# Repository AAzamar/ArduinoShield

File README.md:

# ArduinoShield
Shield de programación, depurado y prototipado para ESP-01 con Arduino UNO.
Colocar las librerías en el mismo directorio que el proyecto para adquirir adecuadamente las huellas y modelos 3D.

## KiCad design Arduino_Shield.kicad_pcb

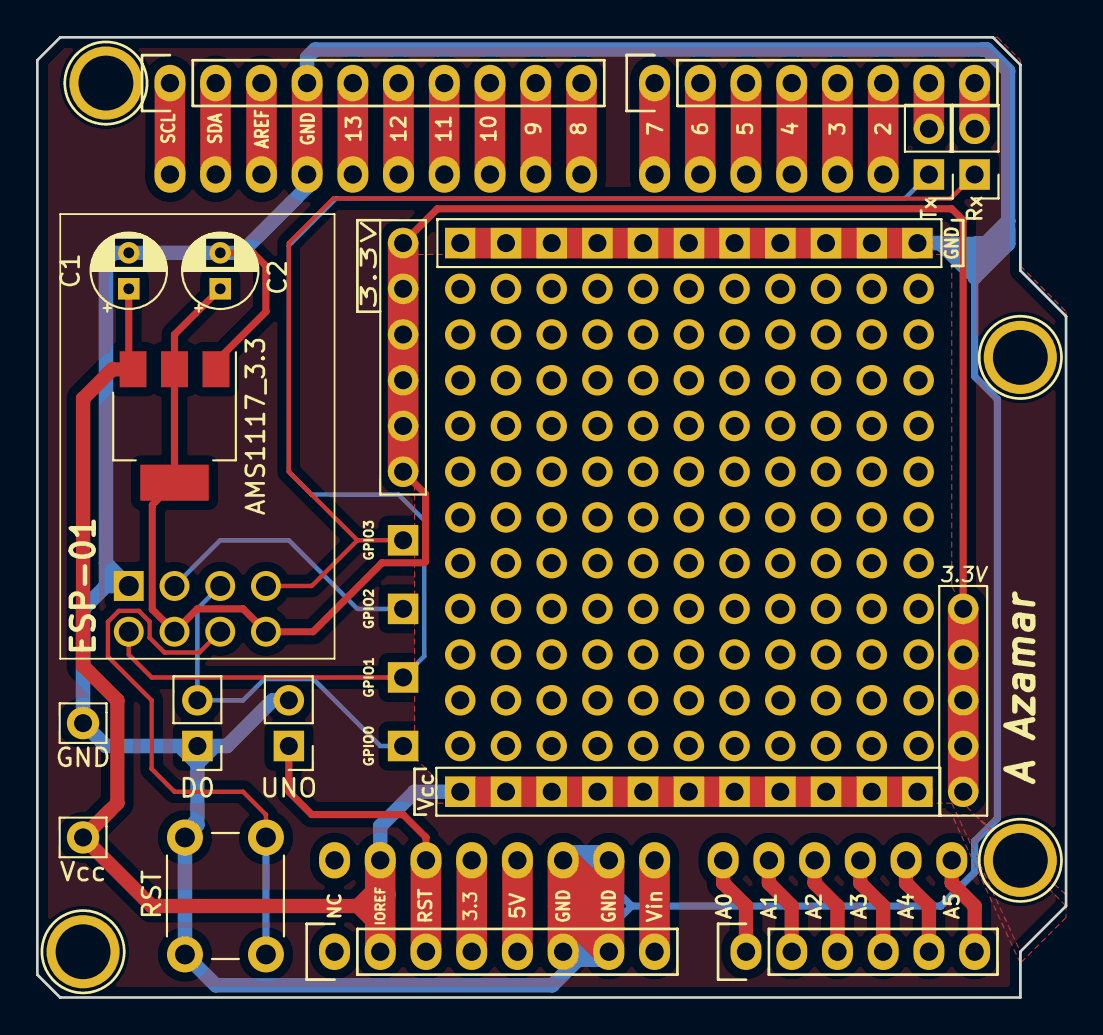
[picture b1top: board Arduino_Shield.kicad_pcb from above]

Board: 2 copper layers, 57.2 x 53.3 mm, 42 parts (0 on the bottom side), 35 nets.

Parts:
AMS1117_3.3: AMS1117-3.3; SOT-223-3_TabPin2
C1, C2: C; CP_Radial_D4.0mm_P2.00mm
D0: Conn_01x02_Male; PinHeader_1x02_P2.54mm_Vertical
ESP-01: ESP-01; ESP01
GND: MountingHole_Pad; Pin_D0.9mm_L10.0mm_W2.4mm_FlatFork
GND2: Conn_01x05; PinHeader_1x05_P2.54mm_Vertical
H2: GPIO0; PinHeader_1x01_P2.54mm_Vertical
H3: GPIO1; PinHeader_1x01_P2.54mm_Vertical
H4: GPIO2; PinHeader_1x01_P2.54mm_Vertical
H5: GPIO3; PinHeader_1x01_P2.54mm_Vertical
J1, J4: Conn_01x11; Pin_11_GND
J2, J3, J5, J6, J7, J8, J9, J10, J11, J12, J13: Conn_01x11; Pin11
P1, P9: Power; Socket_Strip_Arduino_1x08
P2, P10, P12: Analog; Socket_Strip_Arduino_1x06
P3, P11: Digital; Socket_Strip_Arduino_1x10
P4: Digital; Socket_Strip_Arduino_1x08
P5, P6, P7, P8: CONN_01X01; Arduino_1pin
P14: 3.3V; PinHeader_1x06_P2.54mm_Vertical
RST: SW_Push; SW_PUSH_6mm
Rx1: Conn_01x02_Male; PinHeader_1x02_P2.54mm_Vertical
Tx1: Conn_01x02_Male; PinHeader_1x02_P2.54mm_Vertical
UNO: Conn_01x02_Male; PinHeader_1x02_P2.54mm_Vertical
Vcc: MountingHole_Pad; Pin_D0.9mm_L10.0mm_W2.4mm_FlatFork

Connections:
+3V3: P1.4, P9.4
+5V: P1.5, P9.5
/0(Rx): P4.8, Rx1.2
/1(Tx): P4.7, Tx1.2
/2: P4.6, P12.6
/3(**): P4.5, P12.5
/3.3V: AMS1117_3.3.2, C2.1, ESP-01.6, ESP-01.8, GND2.1, GND2.2, GND2.3, GND2.4, GND2.5, P14.1, P14.2, P14.3, P14.4, P14.5, P14.6
/4: P4.4, P12.4
/5(**): P4.3, P12.3
/6(**): P4.2, P12.2
/7: P4.1, P12.1
/8: P3.10, P11.10
/9(**): P3.9, P11.9
/10(**/SS): P3.8, P11.8
/11(**/MOSI): P3.7, P11.7
/12(MISO): P3.6, P11.6
/13(SCK): P3.5, P11.5
/A0: P2.1, P10.1
/A1: P2.2, P10.2
/A2: P2.3, P10.3
/A3: P2.4, P10.4
/A4(SDA): P2.5, P10.5
/A5(SCL): P2.6, P10.6
/AREF: P3.3, P11.3
/GPIO0: D0.2, ESP-01.3, H2.1
/GPIO1: ESP-01.5, H3.1, Tx1.1
/GPIO2: ESP-01.2, H4.1
/GPIO3: ESP-01.4, H5.1, Rx1.1
/IOREF: AMS1117_3.3.3, C1.1, J4.1, J4.2, J4.3, J4.4, J4.5, J4.6, J4.7, J4.8, J4.9, J4.10, J4.11, P1.2, P9.2, Vcc.1
/Reset: P1.3, P9.3, UNO.1
/SCL: P3.1, P11.1
/SDA: P3.2, P11.2
/Vin: P1.8, P9.8
GND: AMS1117_3.3.1, C1.2, C2.2, D0.1, ESP-01.1, GND.1, J1.1, J1.2, J1.3, J1.4, J1.5, J1.6, J1.7, J1.8, J1.9, J1.10, J1.11, P1.6, P1.7, P3.4, P9.6, P9.7, P11.4, RST.2, UNO.2
unnamed: ESP-01.7, RST.1
